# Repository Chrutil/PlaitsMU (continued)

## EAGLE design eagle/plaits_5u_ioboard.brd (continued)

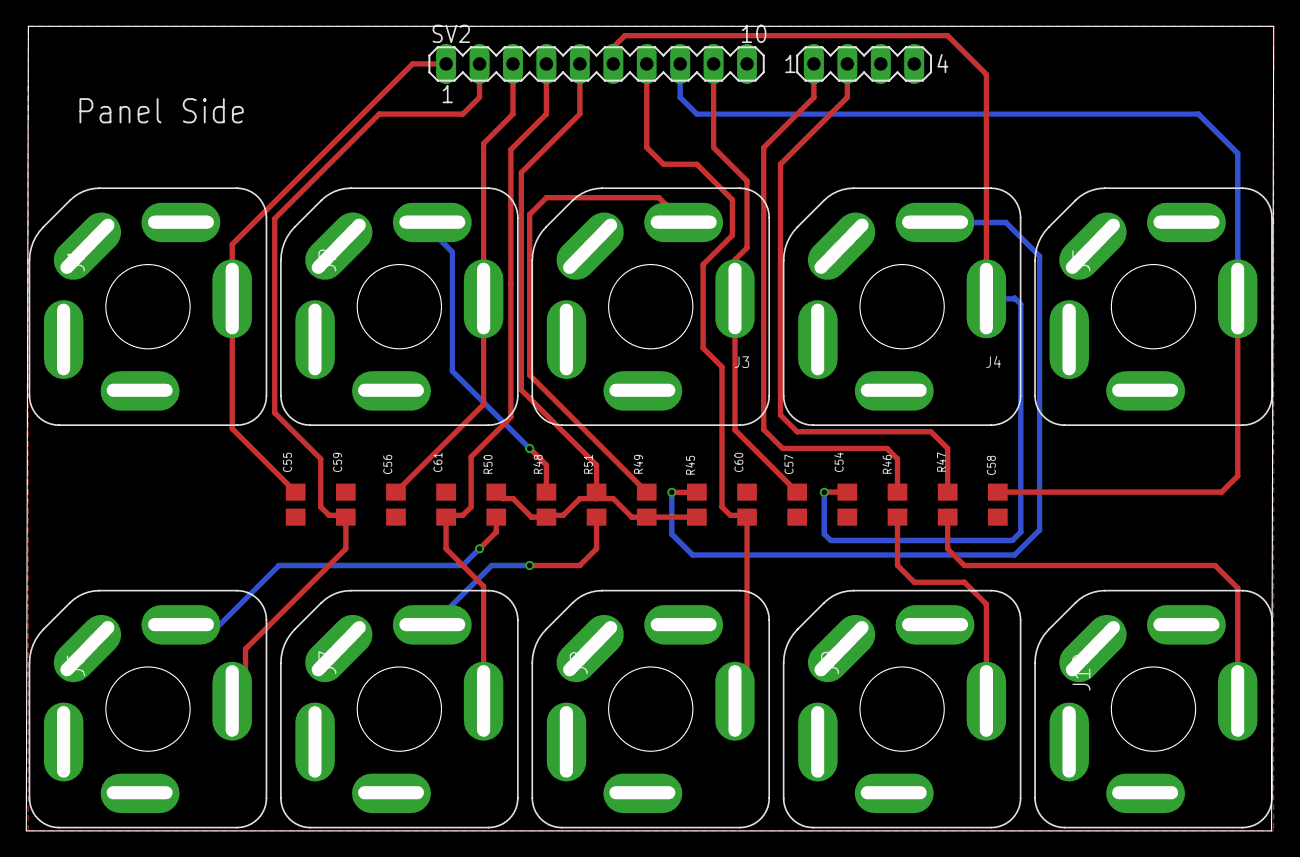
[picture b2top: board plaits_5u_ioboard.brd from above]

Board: 2 copper layers, 94.8 x 61.1 mm, 27 parts (0 on the bottom side), 19 nets.

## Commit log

2019-04-13 :neckbeard: Added .gitattributes & .gitignore files
2019-04-13 Initial commit of Plaits Macro Oscillator ported to MU
2019-04-14 Added BOM with MU component changes
2019-04-14 Updated readme with parts selection information
2019-04-14 Updated BOM and added photos of built module
2019-04-14 Added rudimentary building instructions
